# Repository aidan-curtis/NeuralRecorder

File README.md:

<iframe style="width: 100%" height = "500" src="https://www.youtube.com/embed/SluLUA3ErF0" frameborder="0" allow="accelerometer; autoplay; encrypted-media; gyroscope; picture-in-picture" allowfullscreen></iframe>

## Problem Statement
According to the World Health Organization, up to 50 million people in the world have epilepsy. Of these 50 million, 30% do not respond to medication to keep their seizures under control. These patients are said to have intractable epilepsy, and one of the most effective ways of treating these patients is to record patient EEG data in order to determine the source of the seizures, and then remove the specific part of the brain that is causing the seizures. This process of recording data is invasive and requires implanting electrodes into the brain. These electrodes are wired from inside the brain to a stationary external source that collects the data. The presence of wires causes two main problems: 1) the patients have limited mobility throughout the duration of the data recording and must remain in the hospital for days or even weeks, and 2) the wires are a potential source of infection.

Remaining in the hospital for an extended period of time is extremely expensive, and if the wires were to cause an infection, that cost would only go up. The estimated cost for this procedure is about $10,000 a day. Additionally, being unable to move about unrestricted is detrimental to the patient’s general well-being.

We aim to design a device that can be implanted into a patient’s brain and transmit EEG data wirelessly. Such a device can decrease hospital stay with the possibility of the patient going home for the duration of the recording process, and will drastically decrease the cost of the process. Additionally, even if the patient must remain in the hospital, our device will allow the patient to move about the room freely, which will greatly improve their quality of life. Lastly, our device will also implement novel data compression techniques prior to transmission, which sets our product apart from existing solutions.

## Project Scope
We will build a fully functioning wireless neural recording system that uses data compression to efficiently transmit local field potentials and/or single unit action potential data from patients to a nearby data collection device.

It will contain four major subsystems:
- A power management system
- Frontend interface chip that does signal conditioning
- A wireless link to a receiver
- A novel data compression implementation

With a budget of $2,500 and working between August 29, 2018 and April 11, 2019 we must meet or exceed a minimum set of requirements:
- 48 electrode channels consisting of 6 probes with 8 electrodes each
- A battery life 24 hours or greater
- An ADC resolution of at least 8 bits
- Ability to wirelessly transmit data at least 1 meter
- A Sampling rate of at least 1000 Hz

## Final Design

## Intracranial Testing
<iframe style="width: 100%" height = "500" src="https://www.youtube.com/embed/LJeJShj3aGc" frameborder="0" allow="accelerometer; autoplay; encrypted-media; gyroscope; picture-in-picture" allowfullscreen></iframe>

## ISCAS World Champions
We placed first in the ISCAS Compatition in Sapporo, Japan.

## Full Report
[Download Full Report PDF]( FullReport.pdf )

## Team

- *Aidan Curtis:* arc11 at rice dot edu
- *Sophie D'Amico:* srd5 at rice dot edu
- *Benjamin Klimko:* bhk2 at rice dot edu
- *Irene Zhang:* zz36 at rice dot edu
- *Andres Gomez:* aeg6 at rice dot edu

## Sponsorship
Thanks to Altium for sponsoring our team and providing us with Altium Designer so we can easily and efficiently create custom PCBs for our project.

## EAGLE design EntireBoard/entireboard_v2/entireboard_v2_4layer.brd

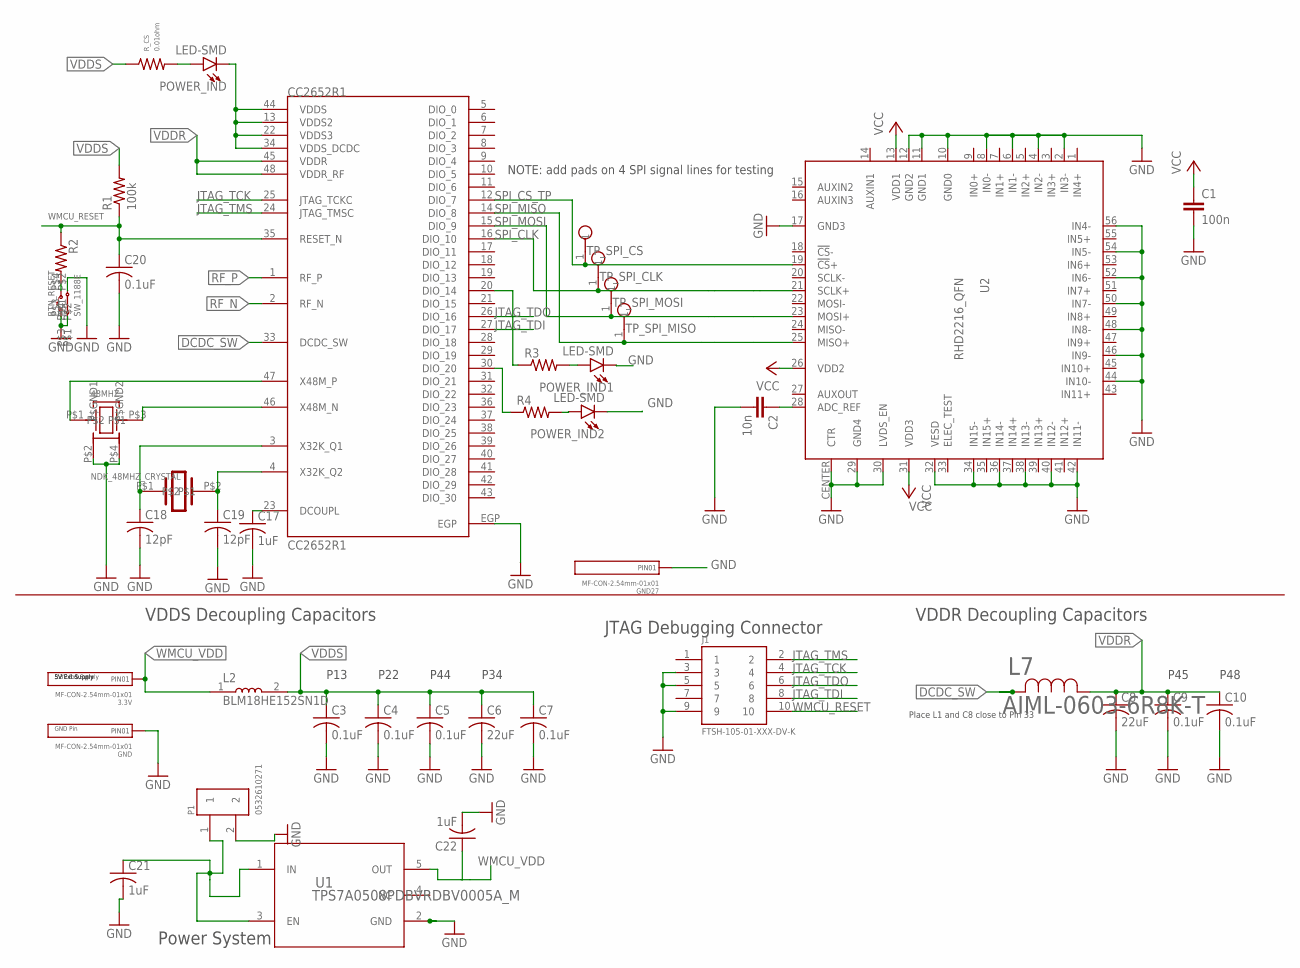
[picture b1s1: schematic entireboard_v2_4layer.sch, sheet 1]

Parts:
3.3V: MF-CON-2.54mm-01x01; PTH_2.54MM_01X01
38.768KHZ: EPSON_32.768KHZ_CRYSTAL; 2-SMD
48MHZ: NDK_48MHZ_CRYSTAL; 4-SMD
BTN_RESET: SW_1188E
C1: 100n; 0402
C2: 10n; 0402
C3, C4, C5, C7, C9, C10, C20: 0.1uF; C0402
C6, C8: 22uF; C0402
C17, C21, C22: 1uF; C0402
C18, C19: 12pF; C0402
CC2652R1: CC2652R1; CC2652R1_QFN-48
GND, GND27: MF-CON-2.54mm-01x01; PTH_2.54MM_01X01
J1: FTSH-105-01-XXX-DV-K
L2: BLM18HE152SN1D; INDC1608X95
L7: AIML-0603-6R8K-T; AIML-0603
P1: 0532610271; MOLEX_0532610271
POWER_IND, POWER_IND1, POWER_IND2: LED-SMD; RHD2000_EVAL_BOARD_0402
R1: 100k; R0402
R2, R3, R4: R-US_R0402; R0402
R_CS: 0.01ohm; R0402
TP_SPI_CLK: RHD2000_EVAL_BOARD_TESTPOINT_SMALL
TP_SPI_CS: RHD2000_EVAL_BOARD_TESTPOINT_SMALL
TP_SPI_MISO: RHD2000_EVAL_BOARD_TESTPOINT_SMALL
TP_SPI_MOSI: RHD2000_EVAL_BOARD_TESTPOINT_SMALL
U1: TPS7A0508PDBVRDBV0005A_M; DBV0005A_M
U2: RHD2216_QFN; QFN56_8_X_8_LARGE

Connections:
DCDC_SW: CC2652R1.33 (DCDC_SW), L7.2
GND: 48MHZ.P$2 (P$GND1), 48MHZ.P$4 (P$GND2), BTN_RESET.P$1, BTN_RESET.P$2, BTN_RESET.P$3, C1.2, C2.2, C3.2, C4.2, C5.2, C6.2, C7.2, C8.2, C9.2, C10.2, C17.2, C18.2, C19.2, C20.2, C21.2, C22.2, CC2652R1.EGP, GND.P$1, GND27.P$1, J1.3, J1.5, J1.9, P1.2, POWER_IND1.2 (C), POWER_IND2.2 (C), U1.2 (GND), U2.2 (IN3-), U2.4 (IN2-), U2.6 (IN1-), U2.8 (IN0-), U2.10 (GND0), U2.11 (GND1), U2.12 (GND2), U2.17 (GND3), U2.29 (GND4), U2.30 (LVDS_EN), U2.32 (VESD), U2.34 (IN15-), U2.36 (IN14-), U2.38 (IN13-), U2.40 (IN12-), U2.42 (IN11-), U2.44 (IN10-), U2.46 (IN9-), U2.48 (IN8-), U2.50 (IN7-), U2.52 (IN6-), U2.54 (IN5-), U2.56 (IN4-), U2.CENTER (CTR); also elsewhere on the board
JTAG_TCK: CC2652R1.25 (JTAG_TCKC), J1.4
JTAG_TDI: CC2652R1.27 (DIO_17), J1.8
JTAG_TDO: CC2652R1.26 (DIO_16), J1.6
JTAG_TMS: CC2652R1.24 (JTAG_TMSC), J1.2
unnamed: C17.1, CC2652R1.23 (DCOUPL)
unnamed: 48MHZ.P$1, CC2652R1.47 (X48M_P)
unnamed: 48MHZ.P$3, CC2652R1.46 (X48M_N)
unnamed: 38.768KHZ.P$1, C18.1, CC2652R1.3 (X32K_Q1)
unnamed: 38.768KHZ.P$2, C19.1, CC2652R1.4 (X32K_Q2)
unnamed: POWER_IND.1 (A), R_CS.P$2
unnamed: C21.1, P1.1, U1.1 (IN), U1.3 (EN)
unnamed: BTN_RESET.P$4, R2.2
unnamed: CC2652R1.20 (DIO_14), R3.1
unnamed: POWER_IND1.1 (A), R3.2
unnamed: CC2652R1.30 (DIO_20), R4.1
unnamed: POWER_IND2.1 (A), R4.2
unnamed: C2.1, U2.28 (ADC_REF)
NC: U1.4 (NC)
RF_N: CC2652R1.2 (RF_N); also elsewhere on the board
RF_P: CC2652R1.1 (RF_P); also elsewhere on the board
SPI_CLK: CC2652R1.16 (DIO_10), TP_SPI_CLK.1, U2.21 (SCLK+)
SPI_CS_TP: CC2652R1.12 (DIO_7), TP_SPI_CS.1, U2.19 (!CS!+)
SPI_MISO: CC2652R1.14 (DIO_8), TP_SPI_MISO.1, U2.25 (MISO+)
SPI_MOSI: CC2652R1.15 (DIO_9), TP_SPI_MOSI.1, U2.23 (MOSI+)
VCC: C1.1, U2.13 (VDD1), U2.26 (VDD2), U2.31 (VDD3)
VDDR: C8.1, C9.1, C10.1, CC2652R1.45 (VDDR), CC2652R1.48 (VDDR_RF), L7.1
VDDS: C3.1, C4.1, C5.1, C6.1, C7.1, CC2652R1.13 (VDDS2), CC2652R1.22 (VDDS3), CC2652R1.34 (VDDS_DCDC), CC2652R1.44 (VDDS), L2.2, POWER_IND.2 (C), R1.2, R_CS.P$1
WMCU_RESET: C20.1, CC2652R1.35 (RESET_N), J1.10, R1.1, R2.1
WMCU_VDD: 3.3V.P$1, C22.1, L2.1, U1.5 (OUT)

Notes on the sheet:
VDDS Decoupling Capacitors
VDDR Decoupling Capacitors
Place L1 and C8 close to Pin 33
P45
P48
P13
P22
P44
P34
JTAG Debugging Connector
NOTE: add pads on 4 SPI signal lines for testing
5V Ext Supply
3.3V Ext Supply
GND Pin
Power System

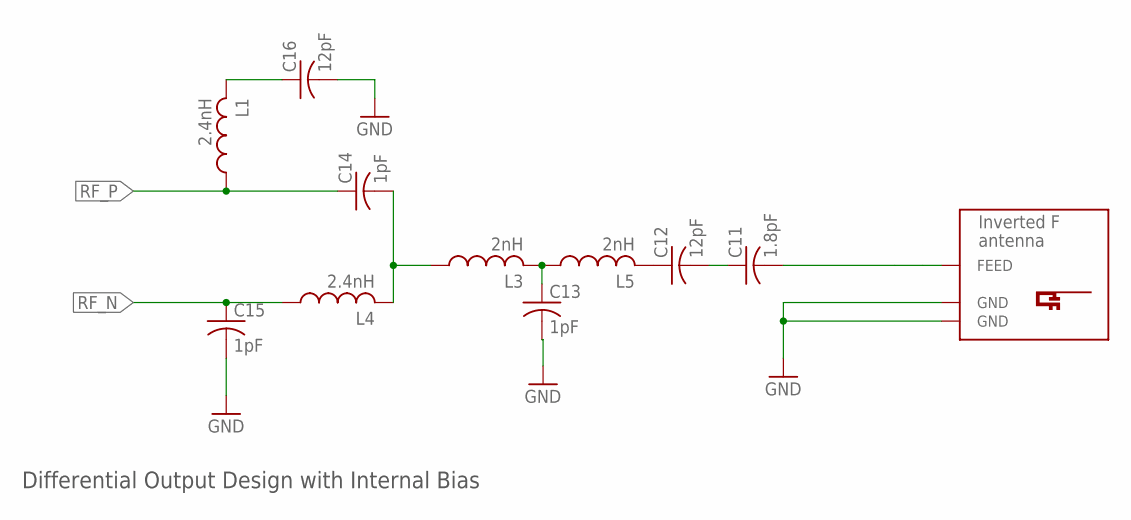
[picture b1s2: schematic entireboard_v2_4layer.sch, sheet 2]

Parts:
C11: 1.8pF; C0402
C12, C16: 12pF; C0402
C13, C14, C15: 1pF; C0402
L1, L4: 2.4nH; L0201
L3, L5: 2nH; L0201
U$2: INVERTED_F_ANTENNA+0; DN007+0

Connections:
GND: C13.2, C15.2, C16.2, U$2.GND, U$2.GND@1 (GND); also elsewhere on the board
unnamed: C11.1, C12.2
unnamed: C12.1, L5.2
unnamed: C13.1, L3.2, L5.1
unnamed: C14.2, L3.1, L4.2
unnamed: C11.2, U$2.FEED
unnamed: C16.1, L1.2
RF_N: C15.1, L4.1; also elsewhere on the board
RF_P: C14.1, L1.1; also elsewhere on the board

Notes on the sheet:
Differential Output Design with Internal Bias

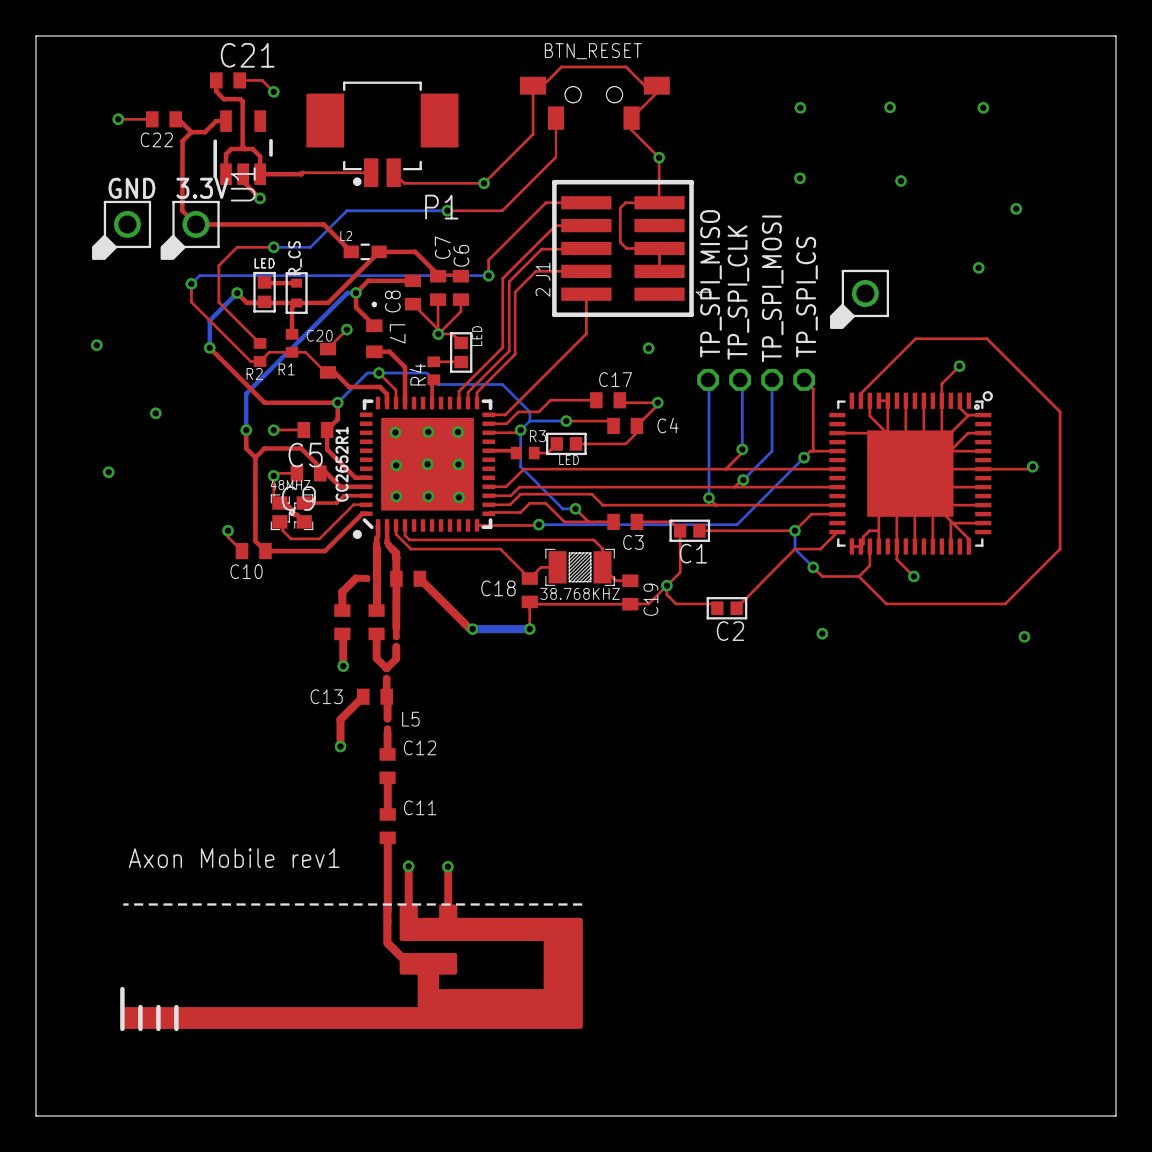
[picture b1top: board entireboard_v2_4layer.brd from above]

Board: 4 copper layers, 60.0 x 60.0 mm, 52 parts (0 on the bottom side), 36 nets.

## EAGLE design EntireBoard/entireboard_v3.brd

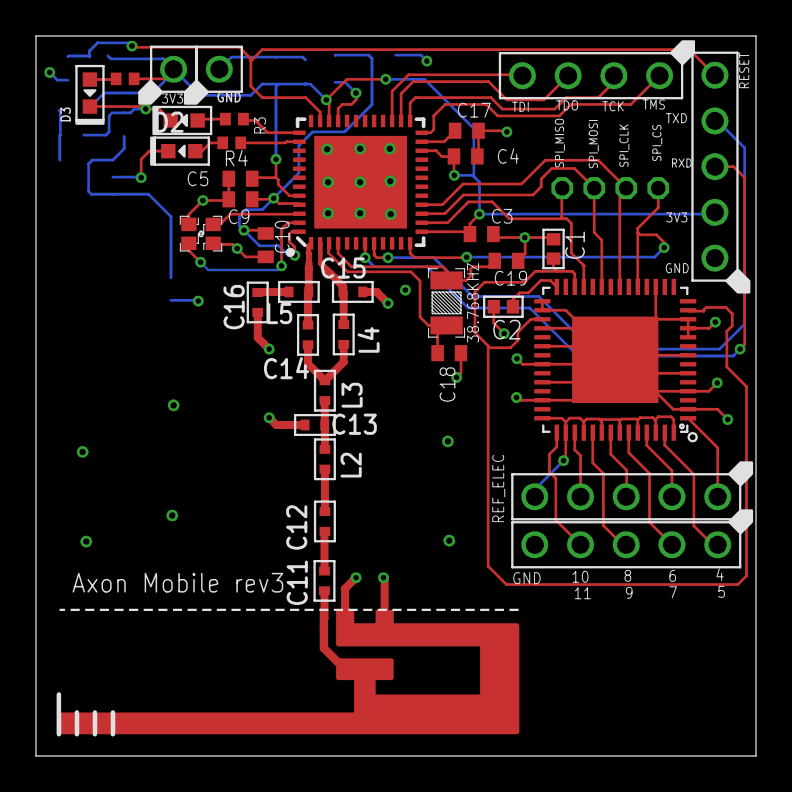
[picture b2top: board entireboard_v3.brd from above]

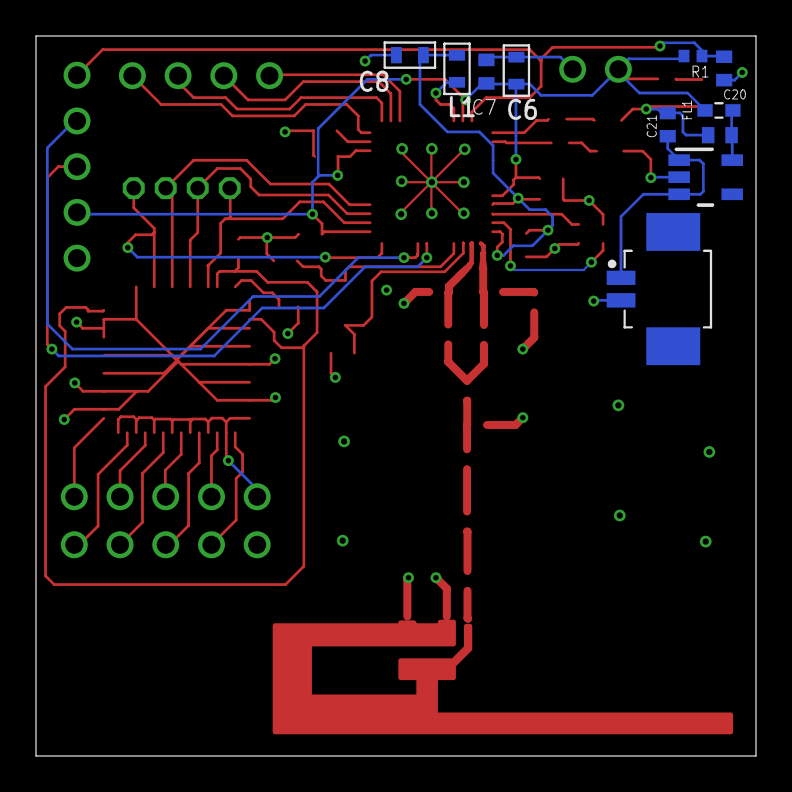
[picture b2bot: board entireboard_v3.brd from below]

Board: 4 copper layers, 40.0 x 40.0 mm, 52 parts (11 on the bottom side), 46 nets.

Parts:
3.3V: MF-CON-2.54mm-01x01; PTH_2.54MM_01X01
38.768KHZ: EPSON_32.768KHZ_CRYSTAL; 2-SMD
48MHZ: NDK_48MHZ_CRYSTAL; 4-SMD
C1: 100n; 0402
C2: 10n; 0402
C3, C4, C5, C7, C9, C10, C20: 0.1uF; C0402
C6, C8: 22uF; C0603
C11: 1.8pF; C0402
C12, C16, C18, C19: 12pF; C0402
C13, C14, C15: 1pF; C0402
C17, C21, C22: 1uF; C0402
D1, D2, D3: LED0603
FL1: BLM18HE152SN1D; INDC1608X95
GND: MF-CON-2.54mm-01x01; PTH_2.54MM_01X01
J1, J2, J4: MF-CON-2.54mm-01x05; PTH_2.54MM_01X05
J3: MF-CON-2.54mm-01x04; PTH_2.54MM_01X04
L1: 6.8uH; L0603
L2, L3: 2nH; L0402
L4, L5: 2.4nH; L0402
P1: 0532610271; MOLEX_0532610271
R1: 100k; R0402
R2, R3, R4: R0402
SPI_CLK: RHD2000_EVAL_BOARD_TESTPOINT_SMALL
SPI_CS: RHD2000_EVAL_BOARD_TESTPOINT_SMALL
SPI_MISO: RHD2000_EVAL_BOARD_TESTPOINT_SMALL
SPI_MOSI: RHD2000_EVAL_BOARD_TESTPOINT_SMALL
U1: TPS7A0508PDBVRDBV0005A_M; DBV0005A_M
U2: RHD2216_QFN; QFN56_8_X_8_LARGE
U$1: CC2652R1; CC2652R1_QFN-48
U$2: INVERTED_F_ANTENNA+0; DN007+0

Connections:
DCDC_SW: L1.P$1, U$1.33
GND: 48MHZ.P$2, 48MHZ.P$4, C1.2, C2.2, C3.2, C4.2, C5.2, C6.P$2, C7.2, C8.P$2, C9.2, C10.2, C13.P$2, C15.P$2, C16.P$2, C17.2, C18.2, C19.2, C20.2, C21.2, C22.2, D1.CATHODE, D2.CATHODE, D3.CATHODE, GND.P$1, J1.P$5, J2.P$1, P1.2, U1.2, U2.2, U2.4, U2.6, U2.8, U2.10, U2.11, U2.12, U2.17, U2.29, U2.30, U2.32, U2.34, U2.36, U2.38, U2.40, U2.CENTER, U$1.EGP, U$2.GND, U$2.GND@1
JTAG_TCK: J3.P$2, U$1.25
JTAG_TDI: J3.P$4, U$1.27
JTAG_TDO: J3.P$3, U$1.26
JTAG_TMS: J3.P$1, U$1.24
unnamed: C17.1, U$1.23
unnamed: D1.ANODE, R3.2
unnamed: 48MHZ.P$1, U$1.47
unnamed: 48MHZ.P$3, U$1.46
unnamed: 38.768KHZ.P$1, C18.1, U$1.3
unnamed: C11.P$1, C12.P$2
unnamed: C12.P$1, L2.P$2
unnamed: C13.P$1, L2.P$1, L3.P$2
unnamed: C14.P$2, L3.P$1, L4.P$2
unnamed: 38.768KHZ.P$2, C19.1, U$1.4
unnamed: C11.P$2, U$2.FEED
unnamed: C16.P$1, L5.P$2
unnamed: R4.1, U$1.38
unnamed: C21.1, P1.1, U1.1, U1.3
unnamed: D2.ANODE, R4.2
unnamed: D3.ANODE, R2.2
unnamed: R3.1, U$1.37
unnamed: J1.P$4, U2.43
unnamed: J4.P$4, U2.45
unnamed: J1.P$3, U2.47
unnamed: J4.P$3, U2.49
unnamed: J1.P$2, U2.51
unnamed: J4.P$2, U2.53
unnamed: J1.P$1, U2.55
unnamed: J4.P$1, U2.1
unnamed: C2.1, U2.28
REF_ELEC: J4.P$5, U2.42, U2.44, U2.46, U2.48, U2.50, U2.52, U2.54, U2.56
RF_N: C15.P$1, L4.P$1, U$1.2
RF_P: C14.P$1, L5.P$1, U$1.1
RXD: J2.P$3, U$1.7
SPI_CLK: SPI_CLK.1, U2.21, U$1.16
SPI_CS_TP: SPI_CS.1, U2.19, U$1.12
SPI_MISO: SPI_MISO.1, U2.25, U$1.14
SPI_MOSI: SPI_MOSI.1, U2.23, U$1.15
TXD: J2.P$4, U$1.8
VCC: C1.1, U2.13, U2.26, U2.31
VDDR: C8.P$1, C9.1, C10.1, L1.P$2, U$1.45, U$1.48
VDDS3V3: 3.3V.P$1, C3.1, C4.1, C5.1, C6.P$1, C7.1, FL1.2, J2.P$2, R1.2, R2.1, U$1.13, U$1.22, U$1.34, U$1.44
WMCU_RESET: C20.1, J2.P$5, R1.1, U$1.35
WMCU_VDD: C22.1, FL1.1, U1.5

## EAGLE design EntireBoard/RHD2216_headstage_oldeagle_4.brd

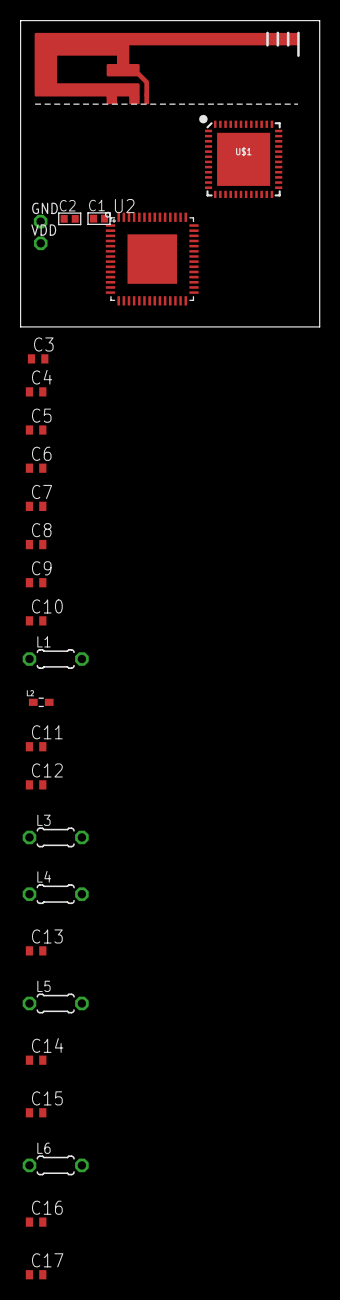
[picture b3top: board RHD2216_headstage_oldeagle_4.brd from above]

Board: 2 copper layers, 29.0 x 29.7 mm, 28 parts (0 on the bottom side), 19 nets, no tracks yet.

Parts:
C1: 100n; 0402
C2: 10n; 0402
C3, C4, C5, C7, C9, C10: 0.1uF; C0402
C6, C8: 22uF; C0402
C11: 1.8pF; C0402
C12, C16: 12pF; C0402
C13, C14, C15: 1pF; C0402
C17: 1uF; C0402
GND: TESTPOINT_SMALL
L1: 6.8uH; 0204/5
L2: BLM18HE152SN1D; INDC1608X95
L3, L4: 2nH; 0204/5
L5, L6: 2.4nH; 0204/5
U2: RHD2216_QFN; QFN56_8_X_8_LARGE
U$1: CC2652R1; QFN-48
U$2: INVERTED_F_ANTENNA+0; DN007+0
VDD: TESTPOINT_SMALL

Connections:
DCDC_SW: L1.1, U$1.33
GND: C1.2, C2.2, C3.2, C4.2, C5.2, C6.2, C7.2, C8.2, C9.2, C10.2, C11.2, C13.2, C15.2, C16.2, C17.1, GND.1, U2.2, U2.4, U2.6, U2.8, U2.10, U2.11, U2.12, U2.17, U2.29, U2.30, U2.32, U2.34, U2.36, U2.38, U2.40, U2.42, U2.44, U2.46, U2.48, U2.50, U2.52, U2.54, U2.56, U2.CENTER, U$2.GND, U$2.GND@1
unnamed: U2.23, U$1.15
unnamed: U2.25, U$1.14
unnamed: U2.19, U$1.12
unnamed: U2.21, U$1.16
unnamed: C3.1, C4.1, C5.1, C6.1, C7.1, L2.2
unnamed: C11.1, C12.2
unnamed: C12.1, L3.2
unnamed: C13.1, L3.1, L4.2
unnamed: C14.2, L4.1, L5.2
unnamed: C17.2, U$1.23
unnamed: C16.1, L6.2
unnamed: C2.1, U2.28
RF_N: C15.1, L5.1
RF_P: C14.1, L6.1
VCC: C1.1, U2.13, U2.26, U2.31, VDD.1
VDDR: C8.1, C9.1, C10.1, L1.2, U$1.45, U$1.48
VDDS: U$1.13, U$1.22, U$1.34, U$1.44

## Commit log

2018-09-16 practice push
2018-09-16 truth
2018-09-16 cleanup
2018-09-16 setup
2018-09-16 handy guide to committing from terminal
2018-09-16 cover letter template
2018-09-23 Set theme jekyll-theme-cayman
2018-09-23 team photo
    we're adorable and we also need this for our website
2018-09-23 added team photo
2018-09-23 Fixed info on subsystems
2018-09-25 added team logo
2018-09-25 i'm dumb and forgot what file extensions are
2018-09-25 svg of logo
2018-09-25 trying to be fancy and seeing if an svg looks nice
2018-09-25 correct size svg
2018-09-25 created folder for sponsorship materials plus created documents
2018-09-26 worked on altium sponsorship stuff
2018-09-26 switching back to png...
2018-09-26 ignore
2018-09-26 osort working on custom data
2018-09-27 added compression, decompression, and SDNR metric
2018-09-28 deleted some mat file
2018-10-09 Altium documents
2018-10-11 working compression and profiling
2018-10-11 compiled c code
2018-10-12 code for some SPI data
2018-10-12 little documentation
2018-10-17 arduino code draft untested
2018-10-17 arduino stream data code untested
2018-10-18 starting visualization
2018-10-19 major visualization updates
2018-10-28 added sponsorship section
2018-10-28 how did we write the same thing twice
2018-11-09 added spi folder
2018-11-09 spi stuff
2018-12-29 entire board first iteration
2019-01-02 modify board, add ref doc, add part lib
2019-01-03 add jtag connector, crystal, bill of materials; update project lbr
2019-01-03 add connector, crystals, bom, lbr
2019-01-04 Autoroute
2019-01-12 add headers, testpads, current sense resistors, led
2019-01-12 separate branch for test pads
2019-01-12 not sure what happened to autoroute
2019-01-14 add CCS projects
2019-01-17 board inconsistencies
2019-01-18 file organization
2019-01-18 spi with rf working
2019-01-18 Update EntireBoard/BOM.xlsx
    added battery stuff to BOM
2019-01-20 asdf
2019-01-24 2 layer 6x6 cm board
2019-01-24 BOM quantities updated
2019-01-24 updated BOM quantities
2019-01-24 quantity change to BOM
2019-01-24 BOM changes
2019-01-29 added test LEDs, still 2 layers
2019-01-31 4 layer
2019-01-31 widened traces to get 50 ohm impedance matching
2019-02-01 drc for 4-layer
2019-02-01 remove buffer files
2019-02-01 added more vias to digital side
2019-02-01 finished???
2019-02-13 reading from 16chs
2019-02-22 add rx/tx
2019-02-23 pca stuff
2019-02-24 final 4 layer board (with correct regulator)
2019-03-02 modify schematics, changed parts
2019-03-02 update LED package and JTAG pins
2019-03-07 version 3!! 4x4cm
2019-03-08 add rf settings
2019-03-11 final (??) board v3
2019-04-02 add saleae visualization
2019-04-08 showcase poster v1
2019-04-09 backup rf code
2019-04-10 final showcase poster
2019-04-11 stuff
2019-04-27 latest tx code
2019-04-27 clean up
2019-04-30 all the fuel gauge code
2019-05-01 all the important documentation we did in one neat zip file
2019-07-29 images
